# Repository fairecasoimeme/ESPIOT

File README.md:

# ESPIOT

Capteur de température / humidité WiFi sur pile autonome 1 an à moins de 10 euros

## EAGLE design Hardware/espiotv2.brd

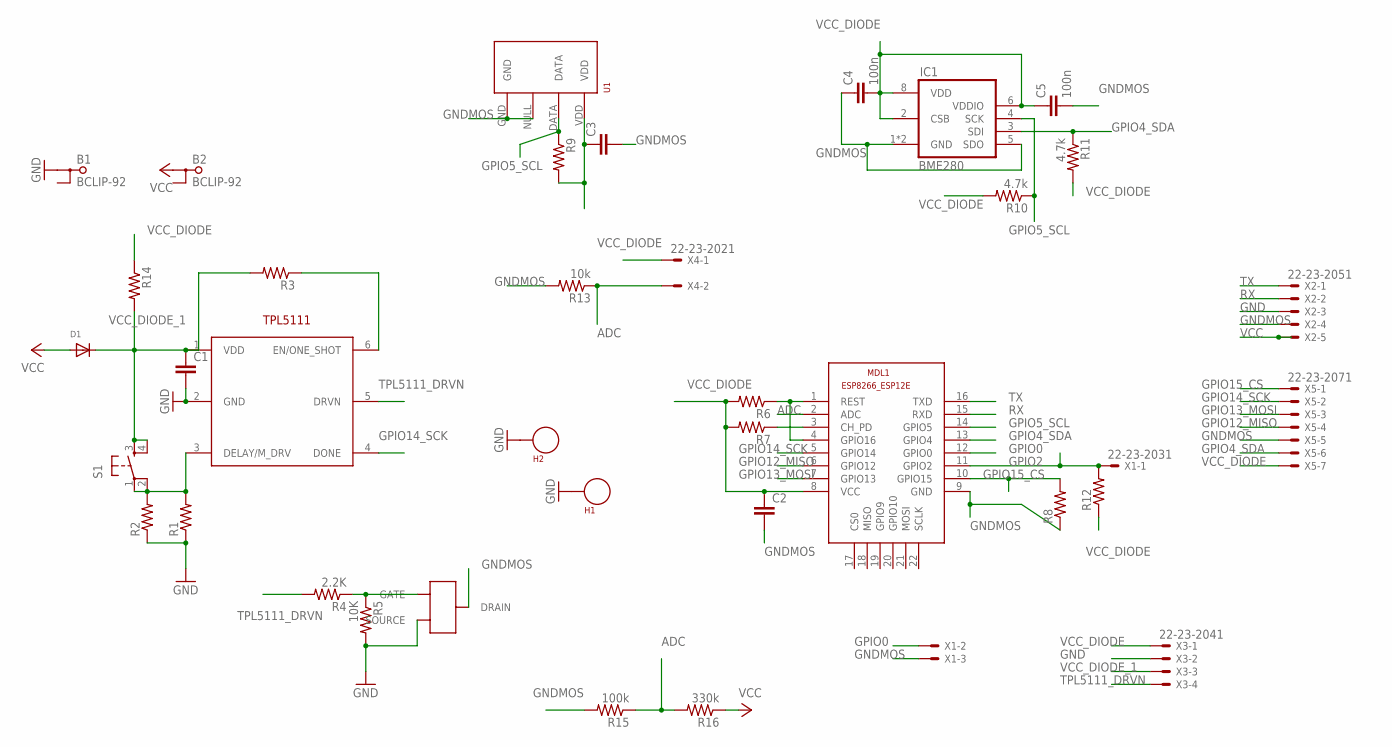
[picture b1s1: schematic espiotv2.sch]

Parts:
B1, B2: BCLIP-92
C1, C2, C3: CAP0603-CAP; 0603-CAP
C4, C5: 100n; 0603-CAP
D1: DIODEDO-1N4148; DO-1N4148
H1, H2: SEW_HOLE; SIMPLE_HOLE
IC1: BME280
MDL1: ESP8266-12EESP8266-ESP12E; ESP8266-ESP12E
R1, R2, R3, R6, R7, R8, R9, R12, R14: RESISTOR0603-RES; 0603-RES
R4: 2.2K; 0603-RES
R5: 10K; 0603-RES
R10, R11: 4.7k; 0603-RES
R13: 10k; 0603-RES
R15: 100k; 0603-RES
R16: 330k; 0603-RES
S1: TAC_SWITCHPTH; TACTILE-PTH
U1: RHT03_DHT-22_AM2302WIRED; AM2302
U$1: TPL5111
U$2: IRLML2502
X1: 22-23-2031
X2: 22-23-2051
X3: 22-23-2041
X4: 22-23-2021
X5: 22-23-2071

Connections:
ADC: MDL1.2 (ADC), R13.1, R15.1, R16.2, X4.2
GND: B1.P$1 (1), C1.2, H1.P$1, H2.P$1, R1.1, R2.1, R5.2, U$1.2 (GND), U$2.S (SOURCE), X2.3, X3.2
GNDMOS: C2.2, C3.2, C4.1, C5.2, IC1.1 (GND), IC1.5 (SDO), IC1.7 (GND), MDL1.9 (GND), R8.1, R13.2, R15.2, U1.GND, U1.NULL, U$2.D (DRAIN), X1.3, X2.4, X5.5
GPIO0: MDL1.12 (GPIO0), X1.2
GPIO2: MDL1.11 (GPIO2), R12.2, X1.1
GPIO4_SDA: IC1.3 (SDI), MDL1.13 (GPIO4), R11.1, X5.6
GPIO5_SCL: IC1.4 (SCK), MDL1.14 (GPIO5), R9.1, R10.1, U1.DATA
GPIO12_MISO: MDL1.6 (GPIO12), X5.4
GPIO13_MOSI: MDL1.7 (GPIO13), X5.3
GPIO14_SCK: MDL1.5 (GPIO14), U$1.4 (DONE), X5.2
GPIO15_CS: MDL1.10 (GPIO15), R8.2, X5.1
unnamed: R4.1, R5.1, U$2.G (GATE)
unnamed: R1.2, R2.2, S1.1, S1.2, U$1.3 (DELAY/M_DRV)
unnamed: MDL1.1 (REST), MDL1.4 (GPIO16), R6.1
unnamed: MDL1.3 (CH_PD), R7.1
unnamed: R3.1, U$1.6 (EN/ONE_SHOT)
RX: MDL1.15 (RXD), X2.2
TPL5111_DRVN: R4.2, U$1.5 (DRVN), X3.4
TX: MDL1.16 (TXD), X2.1
VCC: B2.P$1 (1), D1.A, R16.1, X2.5
VCC_DIODE: C2.1, C3.1, C4.2, C5.1, IC1.2 (CSB), IC1.6 (VDDIO), IC1.8 (VDD), MDL1.8 (VCC), R6.2, R7.2, R9.2, R10.2, R11.2, R12.1, R14.1, U1.VDD, X3.1, X4.1, X5.7
VCC_DIODE_1: C1.1, D1.C, R3.2, R14.2, S1.3, S1.4, U$1.1 (VDD), X3.3

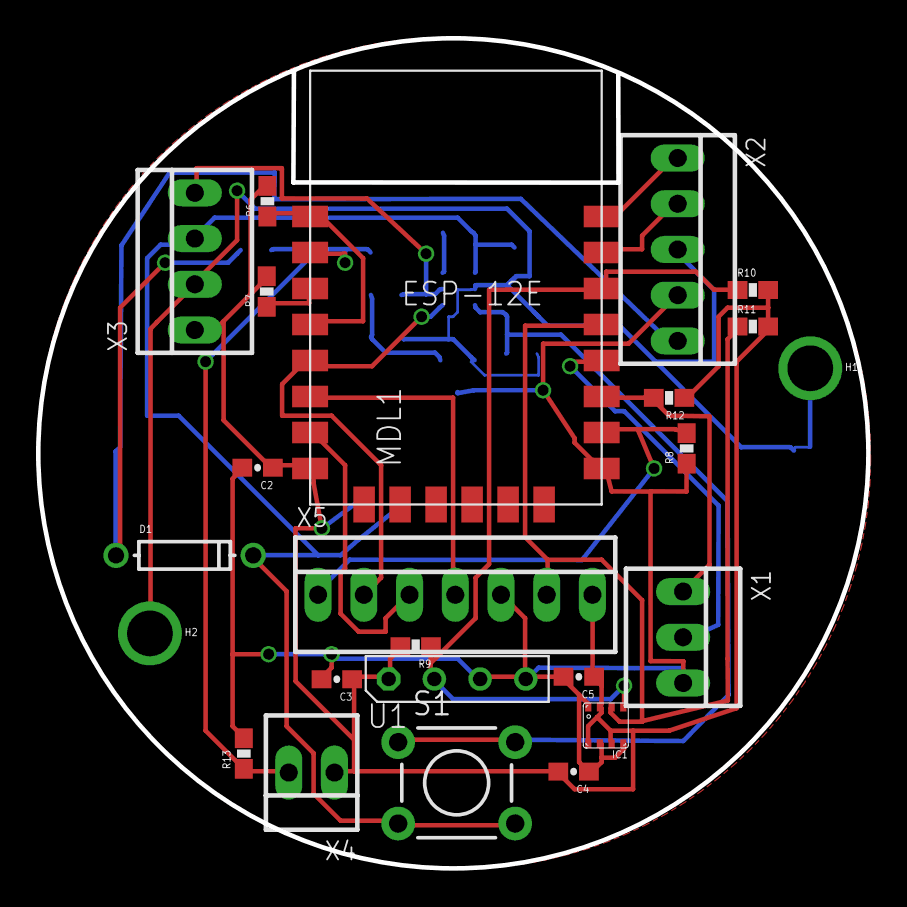
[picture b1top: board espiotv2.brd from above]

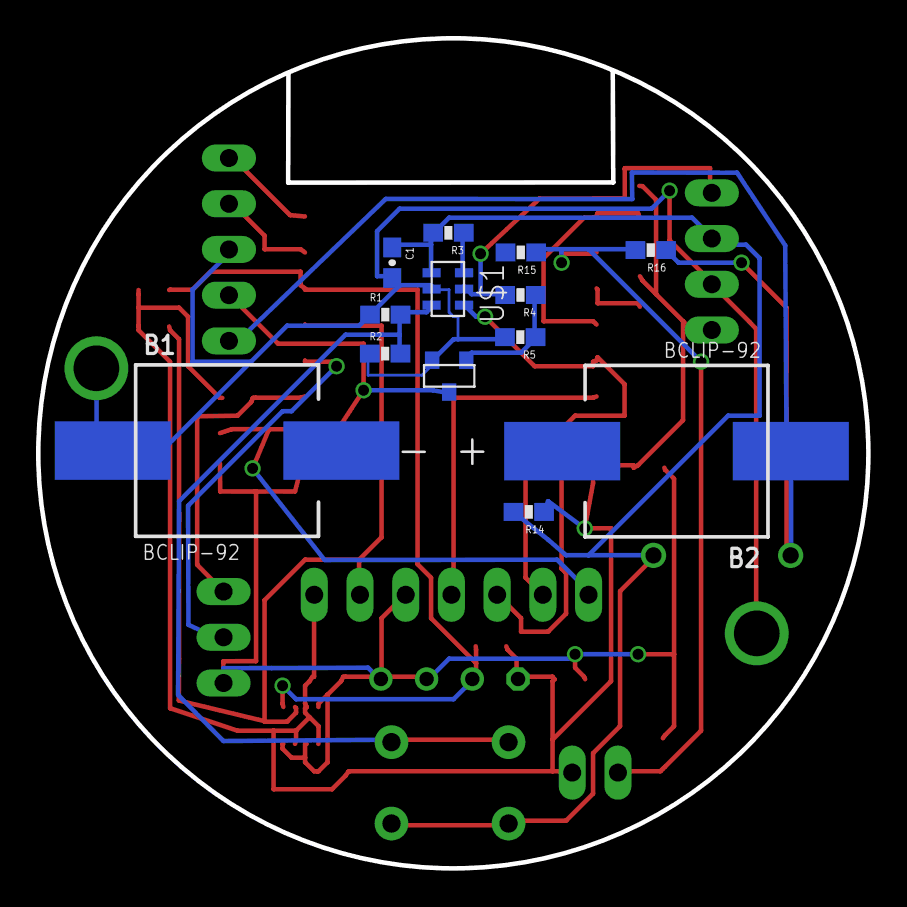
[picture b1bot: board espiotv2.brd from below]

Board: 2 copper layers, 46.1 x 46.1 mm, 37 parts (13 on the bottom side), 22 nets.

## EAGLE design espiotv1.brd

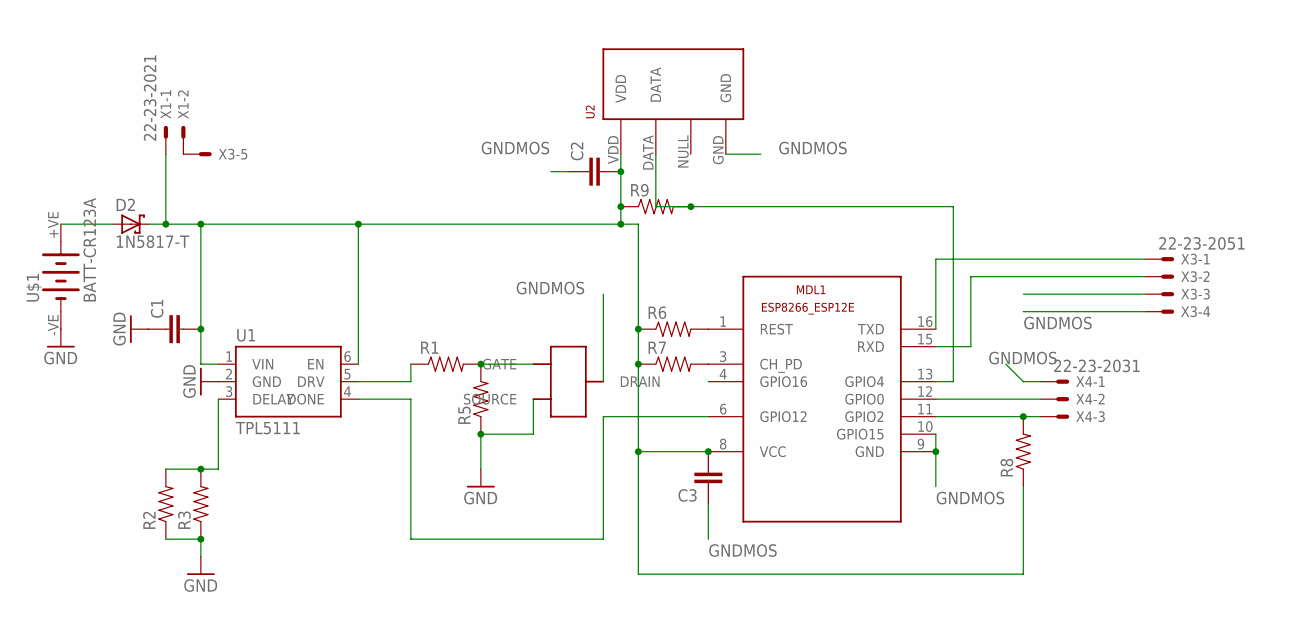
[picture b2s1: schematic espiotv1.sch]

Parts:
C1, C2, C3: CAP0603-CAP; 0603-CAP
D2: 1N5817-T; DO41-7.6
MDL1: ESP8266-12EESP8266-ESP12E; ESP8266-ESP12E
R1, R2, R3, R5, R6, R7, R8, R9: RESISTOR0603-RES; 0603-RES
U1: TPL5111; SOT23-6
U2: RHT03_DHT-22_AM2302RA; RHT03_DHT-22/RA
U$1: BATT-CR123A; KEYSTONE-2/3A
U$3: IRLML2502
X1: 22-23-2021
X3: 22-23-2051
X4: 22-23-2031

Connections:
GND: C1.1, R2.1, R3.1, R5.1, U1.2 (GND), U$1.-VE (-), U$3.S (SOURCE)
GNDMOS: C2.1, C3.1, MDL1.9 (GND), MDL1.10 (GPIO15), U2.GND, U$3.D (DRAIN), X3.3, X3.4, X4.1
unnamed: D2.A, U$1.+VE (+)
unnamed: C1.2, C2.2, C3.2, D2.C, MDL1.8 (VCC), R6.1, R7.1, R8.1, R9.1, U1.1 (VIN), U1.6 (EN), U2.VDD, X1.1
unnamed: R2.2, R3.2, U1.3 (DELAY)
unnamed: R1.1, U1.5 (DRV)
unnamed: R1.2, R5.2, U$3.G (GATE)
unnamed: MDL1.6 (GPIO12), U1.4 (DONE)
unnamed: MDL1.16 (TXD), X3.1
unnamed: MDL1.15 (RXD), X3.2
unnamed: MDL1.1 (REST), R6.2
unnamed: MDL1.3 (CH_PD), R7.2
unnamed: MDL1.13 (GPIO4), R9.2, U2.DATA
unnamed: X1.2, X3.5
unnamed: MDL1.11 (GPIO2), R8.2, X4.3
unnamed: MDL1.12 (GPIO0), X4.2

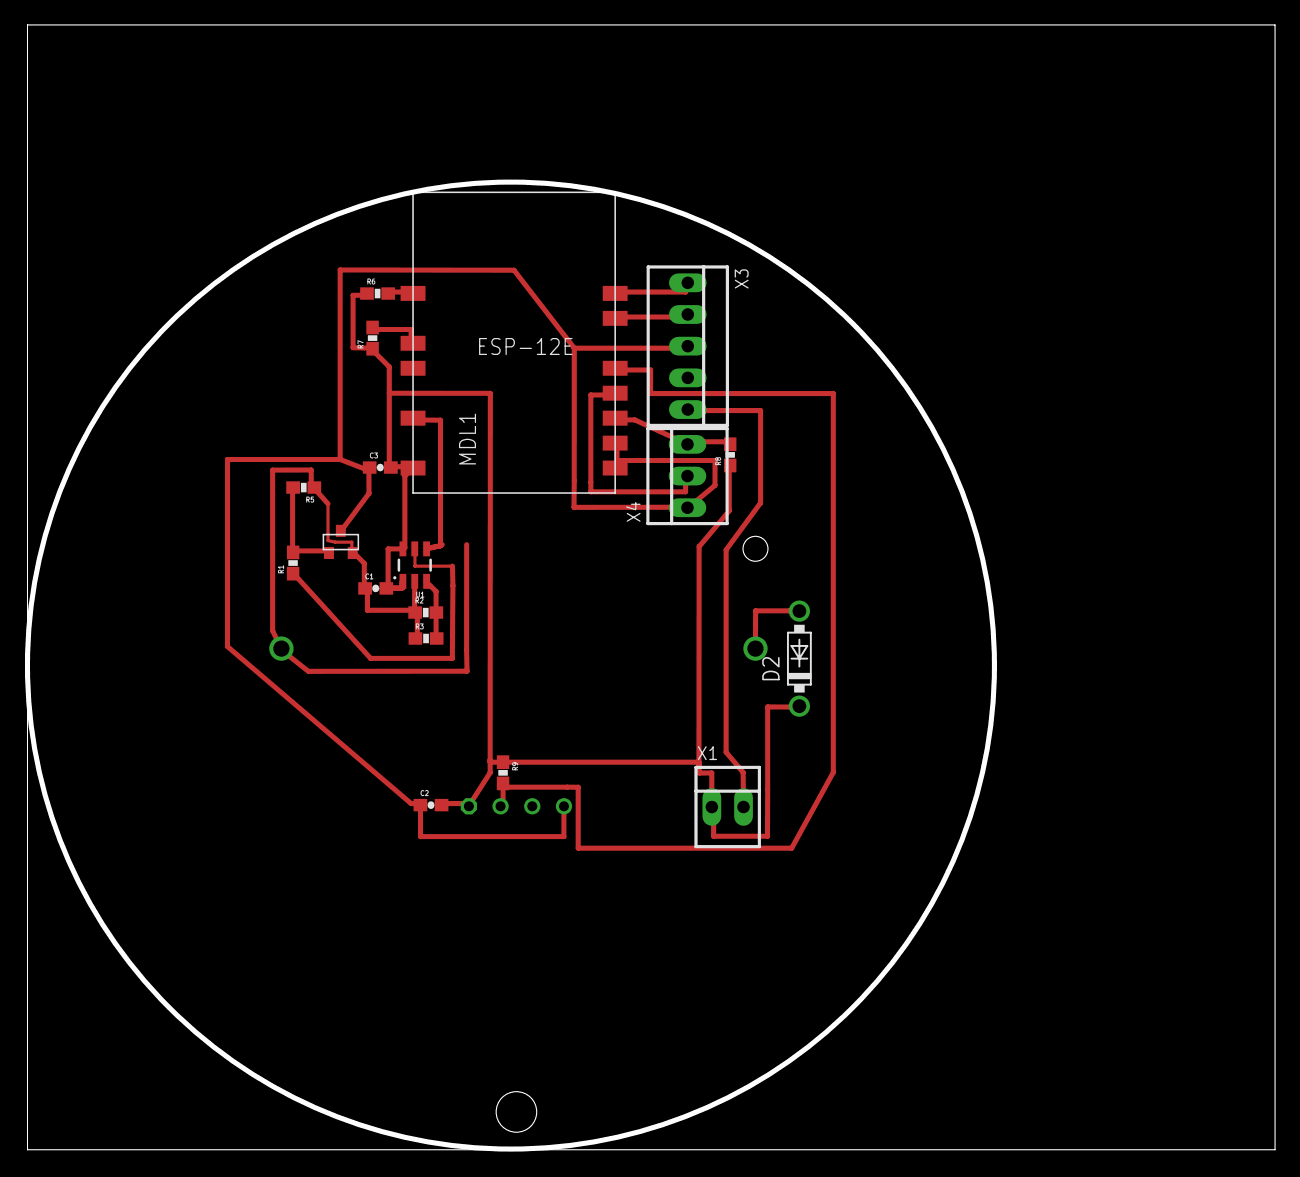
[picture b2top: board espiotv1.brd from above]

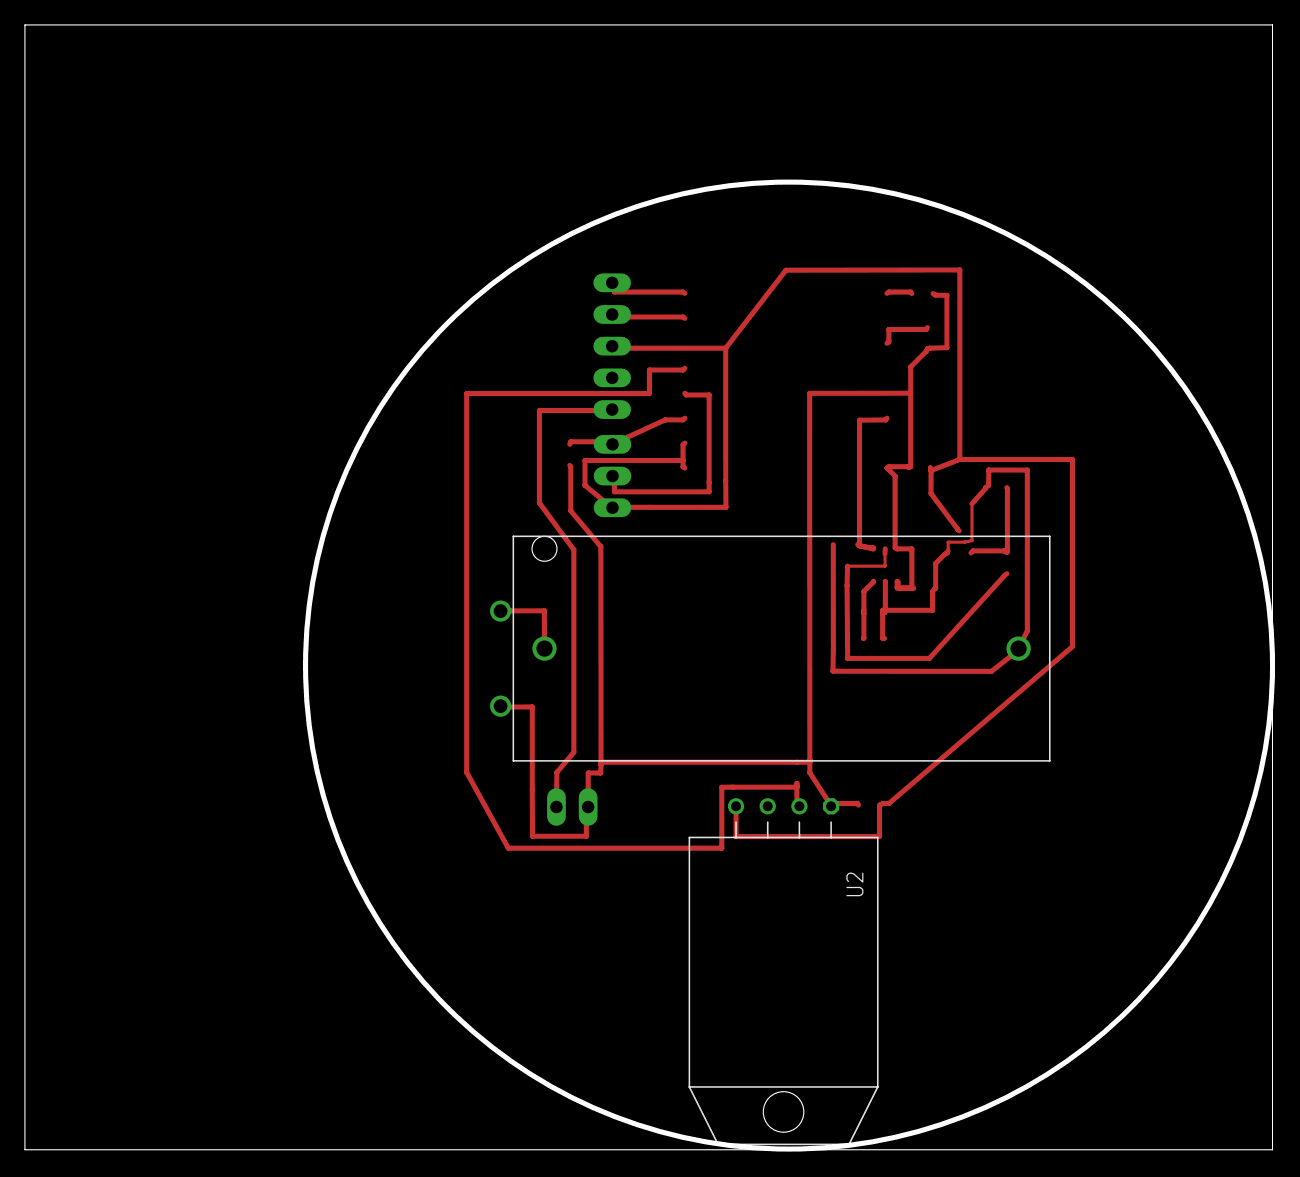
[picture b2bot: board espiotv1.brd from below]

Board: 2 copper layers, 99.8 x 89.9 mm, 20 parts (2 on the bottom side), 16 nets.

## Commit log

2017-01-20 Create Hardware

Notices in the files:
parts and their libraries:
battery-3: This is v1 and is licensed under the Creative Commons (Attribution-Non-Commercial-Share Alike 2.0 UK)
TPL5111: Licensing:Creative Commons ShareAlike 4.0 International - https://creativecommons.org/licenses/by-sa/4.0
keystone_clip: Copyright (C) 2008, Bob Starr
